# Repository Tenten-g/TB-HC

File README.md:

Hackpad. 5 keys, each key should result in its pin number appearing on the OLED. my first project.

Bill of materials:
4x M3x16mm screws
4x M3x5mx4mm heatset inserts
5x MX-Style switches
5x white blank DSA keycaps
1x 0.91 inch OLED display
1x unsoldered Seeed XIAO RP2040

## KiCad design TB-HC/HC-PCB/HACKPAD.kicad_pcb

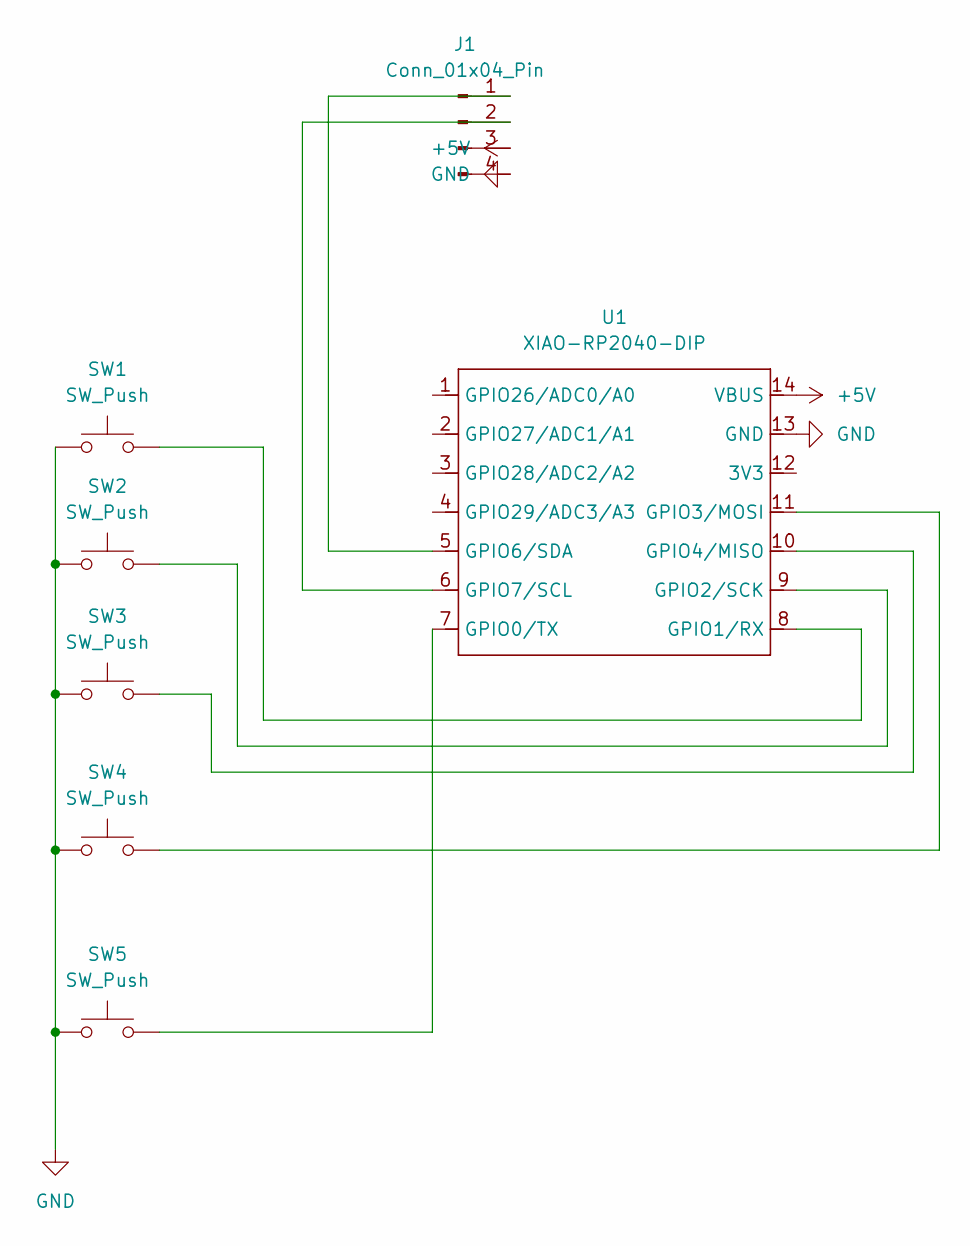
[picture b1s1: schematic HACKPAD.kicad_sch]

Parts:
J1: Conn_01x04_Pin; PinHeader_1x04_P2.54mm_Vertical
SW1, SW2, SW3, SW4, SW5: SW_Push; SW_Cherry_MX_1.00u_PCB
U1: XIAO-RP2040-DIP

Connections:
+5V: J1.3, U1.14 (VBUS)
GND: J1.4, SW1.1, SW2.1, SW3.1, SW4.1, SW5.1, U1.13 (GND)
unnamed: J1.1, U1.5 (GPIO6/SDA)
unnamed: J1.2, U1.6 (GPIO7/SCL)
unnamed: SW5.2, U1.7 (GPIO0/TX)
unnamed: SW1.2, U1.8 (GPIO1/RX)
unnamed: SW2.2, U1.9 (GPIO2/SCK)
unnamed: SW4.2, U1.11 (GPIO3/MOSI)
unnamed: SW3.2, U1.10 (GPIO4/MISO)

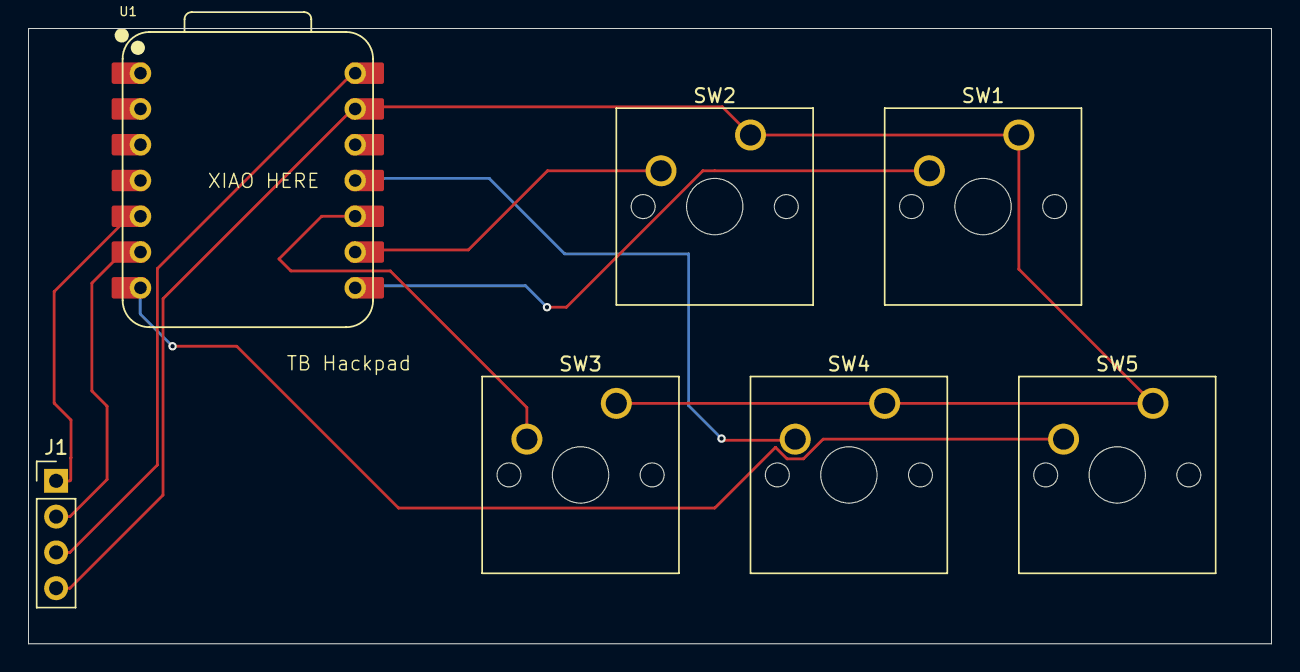
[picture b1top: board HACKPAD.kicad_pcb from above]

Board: 2 copper layers, 88.2 x 43.7 mm, 7 parts (0 on the bottom side), 9 nets.
